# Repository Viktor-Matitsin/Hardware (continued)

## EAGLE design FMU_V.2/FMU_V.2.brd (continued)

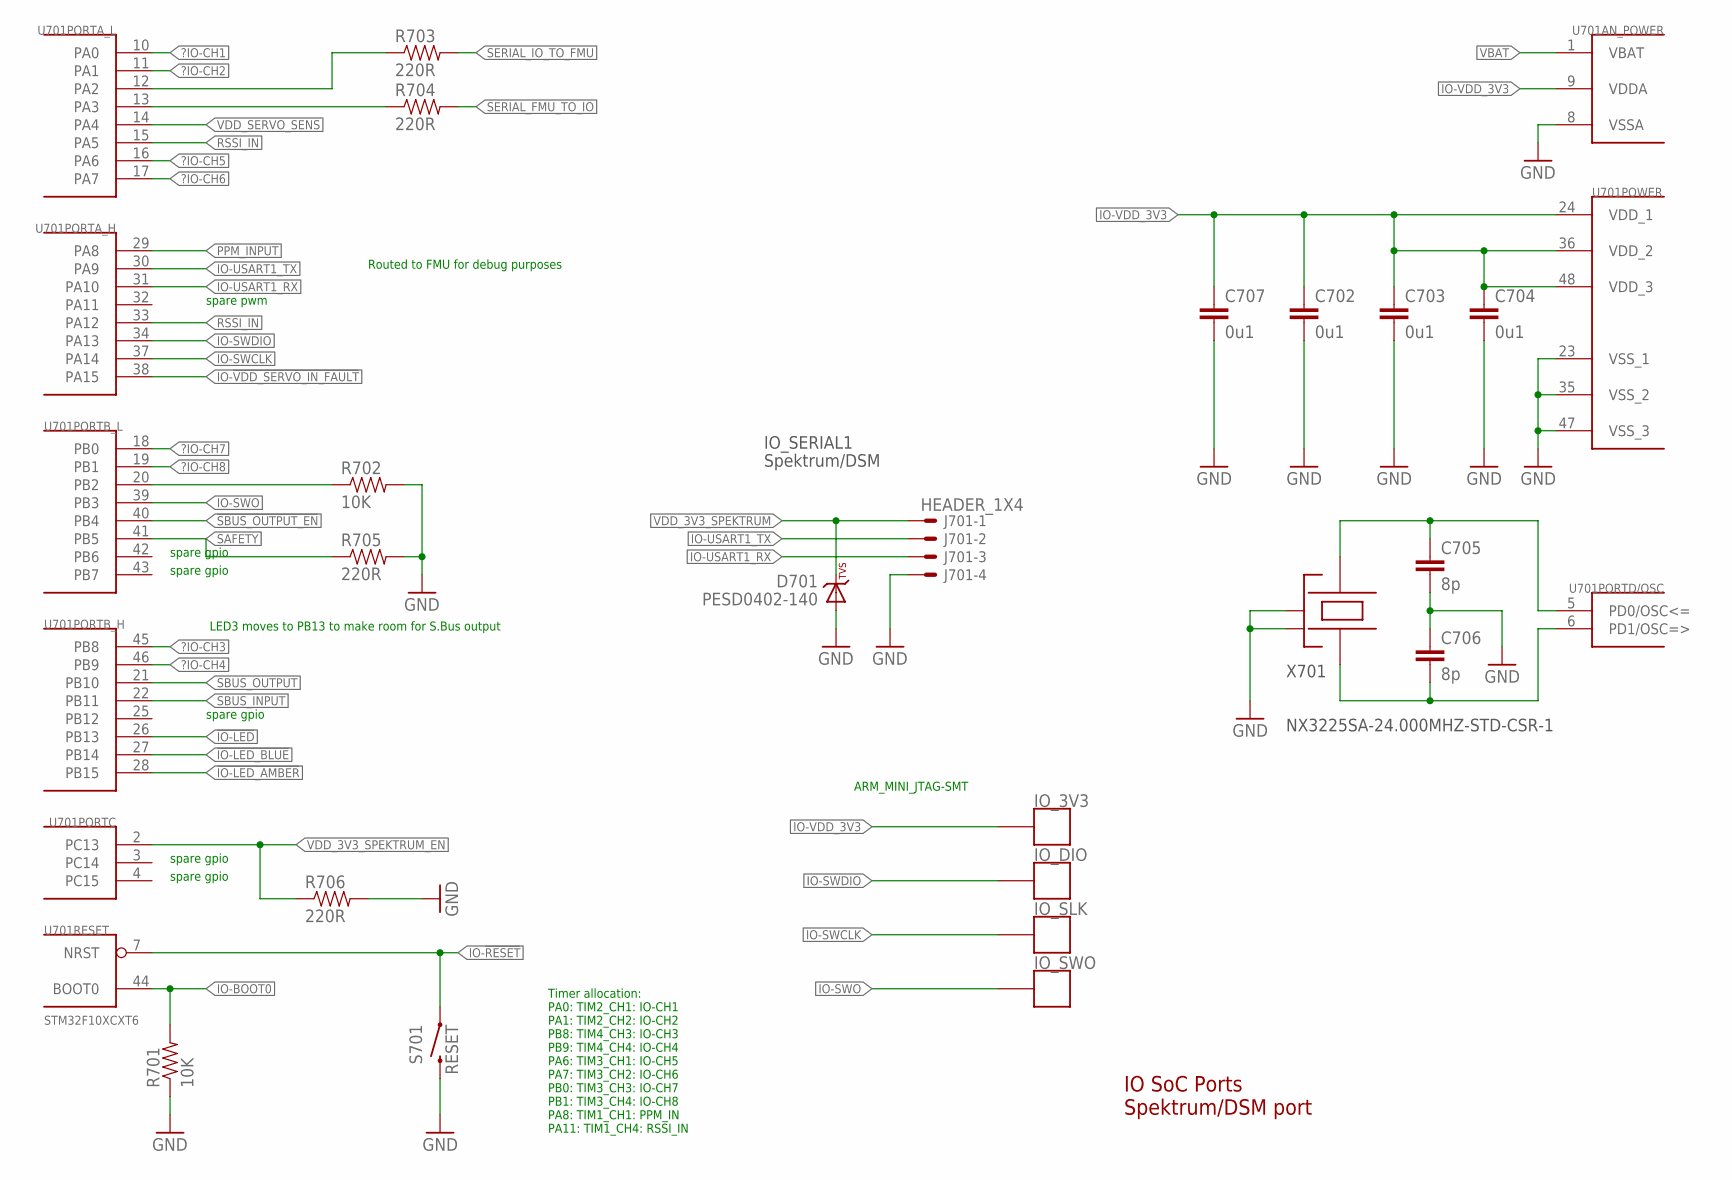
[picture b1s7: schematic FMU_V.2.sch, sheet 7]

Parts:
C702, C703, C704, C707: 0u1; 0603-CAP
C705, C706: 8p; 0603-CAP
D701: PESD0402-140; 0402-TVS; PARTNO PESD0402-140
IO_3V3: PAD.04; PAD.04X.04
IO_DIO: PAD.04; PAD.04X.04
IO_SLK: PAD.04; PAD.04X.04
IO_SWO: PAD.04; PAD.04X.04
J701: HEADER_1X4; HEADER_2.54MM-1X04
R701, R702: 10K; 0603-RES
R703, R704, R705, R706: 220R; 0603-RES
S701: RESET; EVQP7J01K; PARTNO EVQ-P7J01P
U701: STM32F10XCXT6; TQFP48; PARTNO STM32F100C8T6B
X701: NX3225SA-24.000MHZ-STD-CSR-1; OSCILLATOR-3.2X2.5; PARTNO NX3225SA-24.000000MHZ

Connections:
!IO-LED: U701.26 (PB13)
!IO-LED_AMBER: U701.28 (PB15); also elsewhere on the board
!IO-LED_BLUE: U701.27 (PB14); also elsewhere on the board
!SBUS_OUTPUT_EN: U701.40 (PB4)
?IO-CH1: U701.10 (PA0)
?IO-CH2: U701.11 (PA1)
?IO-CH3: U701.45 (PB8)
?IO-CH4: U701.46 (PB9)
?IO-CH5: U701.16 (PA6)
?IO-CH6: U701.17 (PA7)
?IO-CH7: U701.18 (PB0)
?IO-CH8: U701.19 (PB1)
GND: C702.P$2 (2), C703.P$2 (2), C704.P$2 (2), C705.P$2 (2), C706.P$1 (1), C707.P$2 (2), D701.A, J701.4, R701.1, R702.2, R705.2, R706.2, S701.B3 (2), U701.8 (VSSA), U701.23 (VSS_1), U701.35 (VSS_2), U701.47 (VSS_3), X701.2 (NC_2), X701.4 (NC_4); also elsewhere on the board
IO-!RESET: S701.A1 (1), U701.7 (NRST)
IO-!VDD_SERVO_IN_FAULT: U701.38 (PA15)
IO-BOOT0: R701.2, U701.44 (BOOT0); also elsewhere on the board
IO-BOOT1: R702.1, U701.20 (PB2)
IO-SWCLK: IO_SLK.P$1, U701.37 (PA14)
IO-SWDIO: IO_DIO.P$1, U701.34 (PA13)
IO-SWO: IO_SWO.P$1, U701.39 (PB3)
IO-USART1_RX: J701.3, U701.31 (PA10)
IO-USART1_TX: J701.2, U701.30 (PA9); also elsewhere on the board
IO-VDD_3V3: C702.P$1 (1), C703.P$1 (1), C704.P$1 (1), C707.P$1 (1), IO_3V3.P$1, U701.9 (VDDA), U701.24 (VDD_1), U701.36 (VDD_2), U701.48 (VDD_3); also elsewhere on the board
unnamed: R704.1, U701.13 (PA3)
unnamed: R703.1, U701.12 (PA2)
unnamed: C706.P$2 (2), U701.6 (PD1/OSC=>), X701.1
unnamed: C705.P$1 (1), U701.5 (PD0/OSC<=), X701.3
PPM_INPUT: U701.29 (PA8)
RSSI_IN: U701.15 (PA5), U701.33 (PA12)
SAFETY: R705.1, U701.41 (PB5)
SBUS_INPUT: U701.22 (PB11)
SBUS_OUTPUT: U701.21 (PB10)
SERIAL_FMU_TO_IO: R704.2; also elsewhere on the board
SERIAL_IO_TO_FMU: R703.2; also elsewhere on the board
VBAT: U701.1 (VBAT); also elsewhere on the board
VDD_3V3_SPEKTRUM: D701.C, J701.1; also elsewhere on the board
VDD_3V3_SPEKTRUM_EN: R706.1, U701.2 (PC13)
VDD_SERVO_SENS: U701.14 (PA4); also elsewhere on the board

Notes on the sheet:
IO SoC Ports Spektrum/DSM port
LED3 moves to PB13 to make room for S.Bus output
Routed to FMU for debug purposes
IO_SERIAL1
Spektrum/DSM
Timer allocation: PA0: TIM2_CH1: IO-CH1 PA1: TIM2_CH2: IO-CH2 PB8: TIM4_CH3: IO-CH3 PB9: TIM4_CH4: IO-CH4 PA6: TIM3_CH1: IO-CH5 PA7: TIM3_CH2: IO-CH6 PB0: TIM3_CH3: IO-CH7 PB1: TIM3_CH4: IO-CH8 PA8: TIM1_CH1: PPM_IN PA11: TIM1_CH4: RSSI_IN
spare pwm
spare gpio
ARM_MINI_JTAG-SMT

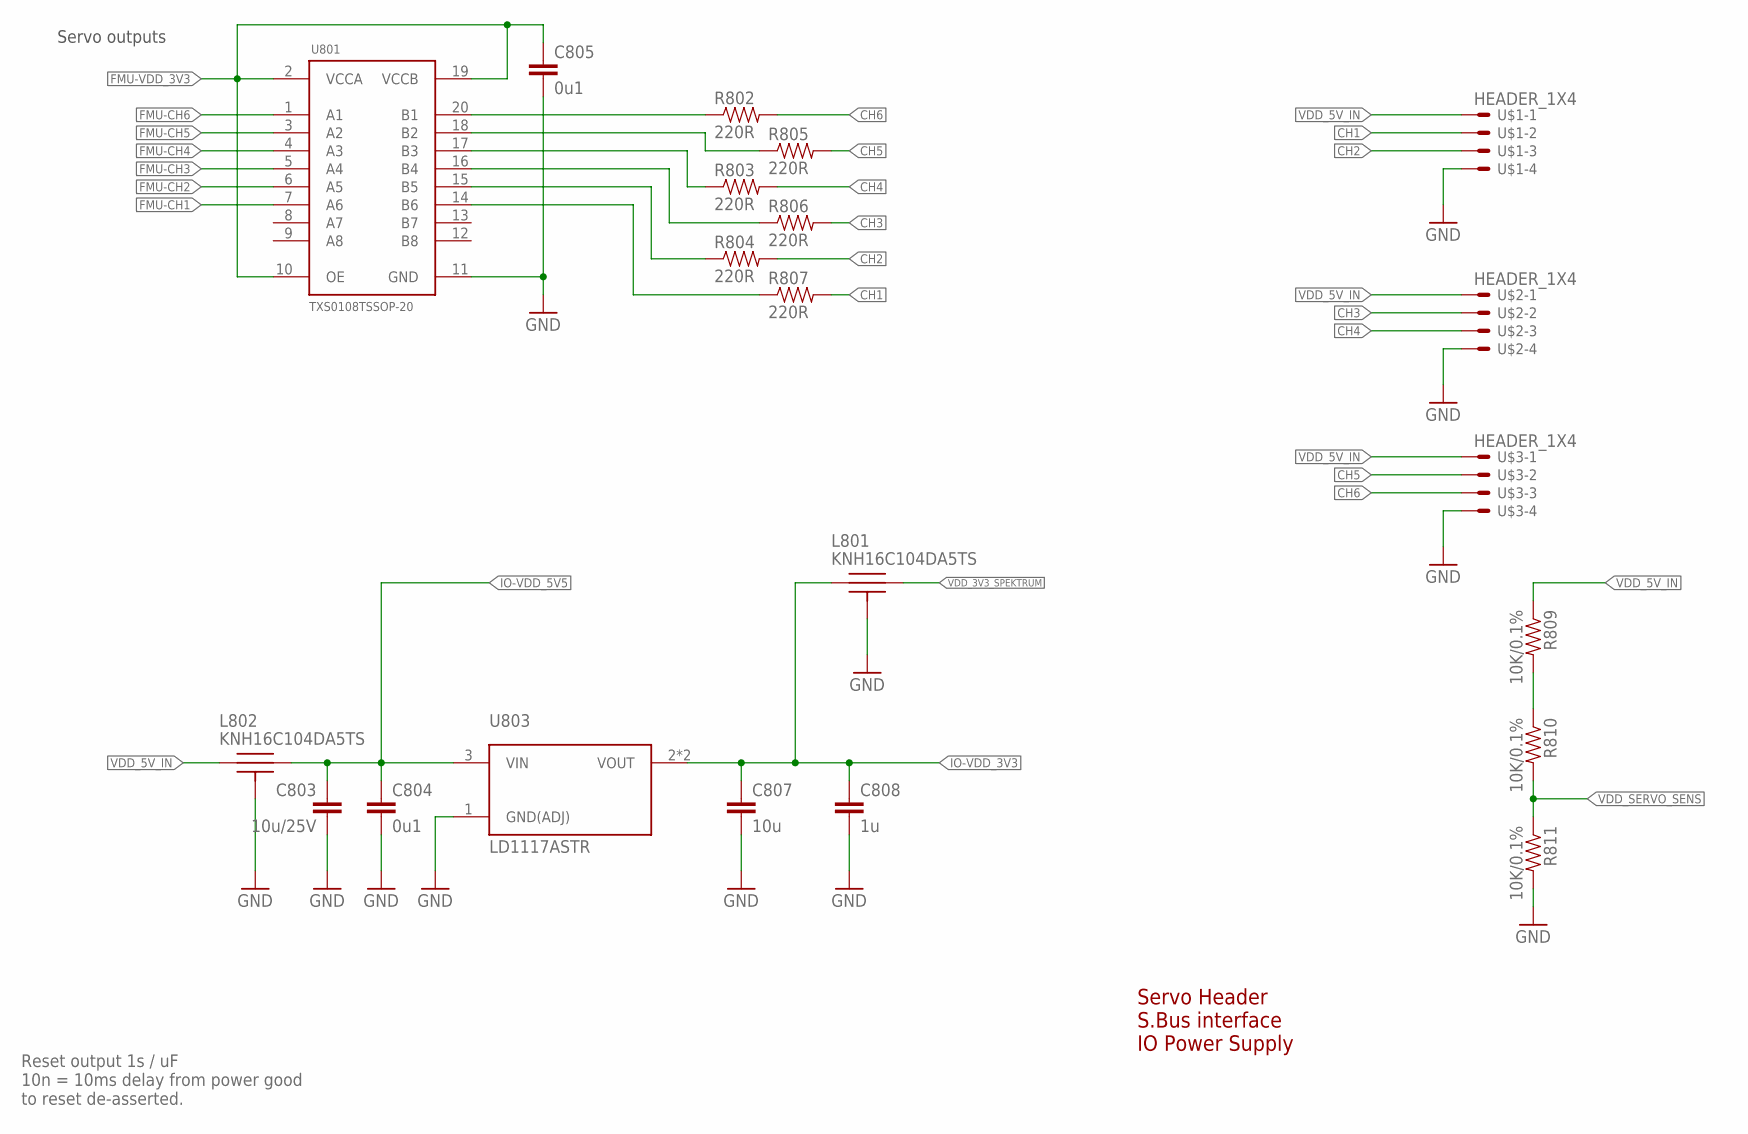
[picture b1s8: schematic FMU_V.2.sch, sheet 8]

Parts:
C803: 10u/25V; 0805-CAP
C804, C805: 0u1; 0603-CAP
C807: 10u; 0603-CAP
C808: 1u; 0603-CAP
L801, L802: KNH16C104DA5TS; KYOCERA-KNH16-DA
R802, R803, R804, R805, R806, R807: 220R; 0603-RES
R809, R810, R811: 10K/0.1%; 0603-RES
U801: TXS0108TSSOP-20; R-PDSO-G20
U803: LD1117ASTR; SOT-223
U$1, U$2, U$3: HEADER_1X4; HEADER_2.54MM-1X04

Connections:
CH1: R807.2, U$1.2
CH2: R804.2, U$1.3
CH3: R806.2, U$2.2
CH4: R803.2, U$2.3
CH5: R805.2, U$3.2
CH6: R802.2, U$3.3
FMU-CH1: U801.7 (A6); also elsewhere on the board
FMU-CH2: U801.6 (A5); also elsewhere on the board
FMU-CH3: U801.5 (A4); also elsewhere on the board
FMU-CH4: U801.4 (A3); also elsewhere on the board
FMU-CH5: U801.3 (A2); also elsewhere on the board
FMU-CH6: U801.1 (A1); also elsewhere on the board
FMU-VDD_3V3: C805.P$1 (1), U801.2 (VCCA), U801.10 (OE), U801.19 (VCCB); also elsewhere on the board
GND: C803.P$2 (2), C804.P$2 (2), C805.P$2 (2), C807.P$2 (2), C808.P$2 (2), L801.P$3, L801.P$4, L801.P$5, L802.P$3, L802.P$4, L802.P$5, R811.2, U801.11 (GND), U803.1 (GND(ADJ)), U$1.4, U$2.4, U$3.4; also elsewhere on the board
IO-VDD_3V3: C807.P$1 (1), C808.P$1 (1), L801.P$1, U803.2 (VOUT), U803.4 (VOUT); also elsewhere on the board
IO-VDD_5V5: C803.P$1 (1), C804.P$1 (1), L802.P$2, U803.3 (VIN); also elsewhere on the board
unnamed: R809.2, R810.1
unnamed: R802.1, U801.20 (B1)
unnamed: R805.1, U801.18 (B2)
unnamed: R803.1, U801.17 (B3)
unnamed: R806.1, U801.16 (B4)
unnamed: R804.1, U801.15 (B5)
unnamed: R807.1, U801.14 (B6)
VDD_3V3_SPEKTRUM: L801.P$2; also elsewhere on the board
VDD_5V_IN: L802.P$1, R809.1, U$1.1, U$2.1, U$3.1; also elsewhere on the board
VDD_SERVO_SENS: R810.2, R811.1; also elsewhere on the board

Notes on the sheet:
Servo Header S.Bus interface IO Power Supply
Servo outputs
Reset output 1s / uF 10n = 10ms delay from power good to reset de-asserted.

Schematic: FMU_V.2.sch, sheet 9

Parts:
C333, C334: 0u1; 0805-CAP
C901, C902, C903, C904, C905, C906, C907, C908: 22u; 1812-CAP
C909*, C910*, C921*, C922*: CAP0805; 0805-CAP
C911, C912, C923, C924: 330p; 0805-CAP
C913, C914, C918, C920: 0u01; 0805-CAP
C915, C916: 0u47/16V; 0805-CAP
C917, C919: 0u022; 0805-CAP
C925, C926, C927, C929, C930, C931: 100u; 1206-CAP
C928, C932: 33u; 1206-CAP
D901, D902, D903, D904: 6CWQ10FN-M3; DPAK
D909: 30BQ100; SMA-DIODE
J901, J902: HEADER_1X4; HEADER_2.54MM-1X04
L901, L902: DR120-330/33uH; SLF10145
L903, L904: KNH16C104DA5TS; KYOCERA-KNH16-DA; PARTNO KNH16C104DA5TS
LED6: ARG1608GKC/T; 0603-LED
R901, R902: 1M; 0603-RES
R903, R904: 22K/1%; 0603-RES
R905*, R906*, R907*, R908*: RESISTOR0805; 0805
R910, R911: 21K; 0805
R912, R913: 49K9; 0805
R914, R915: 1K65; 0805
R916, R917: 10R; R2512
R918, R919: 5K11; 0805
R921: 330R; 0603-RES
SYNC, SYNC1: PAD.03; PAD.03X.03
U901, U902: LM5005; TSSOP20
U$4: HEADER_1X4; HEADER_2.54MM-1X04

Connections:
BATT_CURRENT_SENS: R903.2; also elsewhere on the board
BATT_VOLTAGE_SENS: R904.2; also elsewhere on the board
CURRENT: L903.P$1, R902.2, U$4.2
GND: C333.P$2 (2), C334.P$2 (2), C901.2, C902.2, C903.2, C904.2, C905.2, C906.2, C907.2, C908.2, C909*.P$2 (2), C910*.P$2 (2), C911.P$2 (2), C912.P$2 (2), C913.P$2 (2), C914.P$2 (2), C915.P$2 (2), C916.P$2 (2), C925.P$2 (2), C926.P$2 (2), C927.P$2 (2), C928.P$2 (2), C929.P$2 (2), C930.P$2 (2), C931.P$2 (2), C932.P$2 (2), J901.3, J901.4, J902.3, J902.4, L903.P$3, L903.P$4, L903.P$5, L904.P$3, L904.P$4, L904.P$5, R901.1, R902.1, R906*.1, R908*.1, R910.1, R911.1, R914.1, R915.1, R916.2, R917.2, R921.1, U901.10 (AGND), U901.13 (PGND1), U901.14 (PGND), U902.10 (AGND), U902.13 (PGND1), U902.14 (PGND), U$4.4; also elsewhere on the board
unnamed: C918.P$1 (1), R912.1
unnamed: LED6.C, R921.2
unnamed: C920.P$1 (1), R913.1
unnamed: C911.P$1 (1), U901.9 (RAMP)
unnamed: D903.1 (A1), D903.3 (A2), U901.15 (IS), U901.16 (IS1)
unnamed: SYNC.P$1, U901.5 (SYNC)
unnamed: C909*.P$1 (1), R905*.1, R906*.2, U901.2 (SD)
unnamed: C913.P$1 (1), U901.11 (SS)
unnamed: D901.1 (A1), D901.3 (A2), J901.1, J901.2
unnamed: C901.1, C902.1, C903.1, C904.1, D901.4 (C), R905*.2, U901.3 (VIN), U901.4 (VIN1)
unnamed: C334.P$1 (1), C929.P$1 (1), C930.P$1 (1), C931.P$1 (1), C932.P$1 (1), D909.A, L902.P$2 (2), LED6.A, R919.2, U902.12 (OUT)
unnamed: C917.P$2 (2), C923.P$1 (1), D903.4 (C), L901.P$1 (1), U901.17 (SW), U901.18 (SW1), U901.19 (PRE)
unnamed: C915.P$1 (1), U901.1 (VCC)
unnamed: L904.P$2, R904.1
unnamed: L903.P$2, R903.1
unnamed: C905.1, C906.1, C907.1, C908.1, D902.4 (C), R907*.2, U902.3 (VIN), U902.4 (VIN1)
unnamed: R910.2, U901.8 (RT)
unnamed: C917.P$1 (1), U901.20 (BST)
unnamed: C923.P$2 (2), R916.1
unnamed: C916.P$1 (1), U902.1 (VCC)
unnamed: C921*.P$1 (1), R912.2, R914.2, R918.1, U901.7 (FB)
unnamed: C918.P$2 (2), C921*.P$2 (2), U901.6 (COMP)
unnamed: R911.2, U902.8 (RT)
unnamed: C914.P$1 (1), U902.11 (SS)
unnamed: C912.P$1 (1), U902.9 (RAMP)
unnamed: SYNC1.P$1, U902.5 (SYNC)
unnamed: C910*.P$1 (1), R907*.1, R908*.2, U902.2 (SD)
unnamed: D902.1 (A1), D902.3 (A2), J902.1, J902.2
unnamed: D904.1 (A1), D904.3 (A2), U902.15 (IS), U902.16 (IS1)
unnamed: C919.P$2 (2), C924.P$1 (1), D904.4 (C), L902.P$1 (1), U902.17 (SW), U902.18 (SW1), U902.19 (PRE)
unnamed: C919.P$1 (1), U902.20 (BST)
unnamed: C924.P$2 (2), R917.1
unnamed: C922*.P$1 (1), R913.2, R915.2, R919.1, U902.7 (FB)
unnamed: C920.P$2 (2), C922*.P$2 (2), U902.6 (COMP)
VDD_5V_IN: C333.P$1 (1), C925.P$1 (1), C926.P$1 (1), C927.P$1 (1), C928.P$1 (1), D909.C, L901.P$2 (2), R918.2, U901.12 (OUT); also elsewhere on the board
VOLTAGE: L904.P$1, R901.2, U$4.3

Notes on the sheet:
Power source selector
1V_+51V
2V_+51V

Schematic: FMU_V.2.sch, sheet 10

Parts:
DM: PAD.04; PAD.04X.04; PARTNO *
DP: OTG_FS_DP; PAD.04X.04; PARTNO *
F-BOOT: PAD.04; PAD.04X.04; PARTNO *
GND: PAD.04; PAD.04X.04; PARTNO *
IO-BOOT0: PAD.04; PAD.04X.04; PARTNO *
JP3, JP4: FIDUCIAL1.5X3; FIDUCIAL-1.5X3
M3_MOUNT1, M3_MOUNT2, M3_MOUNT3, M3_MOUNT4: MOUNT-HOLE3.1MM; MOUNT-HOLE3.1; PARTNO *
VDDA_3V3: PAD.04; PAD.04X.04; PARTNO *
VDD_5V_IN: PAD.04; PAD.04X.04; PARTNO *

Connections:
FMU-BOOT0: F-BOOT.P$1; also elsewhere on the board
GND: GND.P$1; also elsewhere on the board
IO-BOOT0: IO-BOOT0.P$1; also elsewhere on the board
OTG_FS_DM: DM.P$1; also elsewhere on the board
OTG_FS_DP: DP.P$1; also elsewhere on the board
VDD_3V3_SENSORS: VDDA_3V3.P$1; also elsewhere on the board
VDD_5V_IN: VDD_5V_IN.P$1; also elsewhere on the board

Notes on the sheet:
Production Testing Pads
Test and Fiducials
Fiducials for machine vision alignment.
POWER
STATUS AND ANALOG

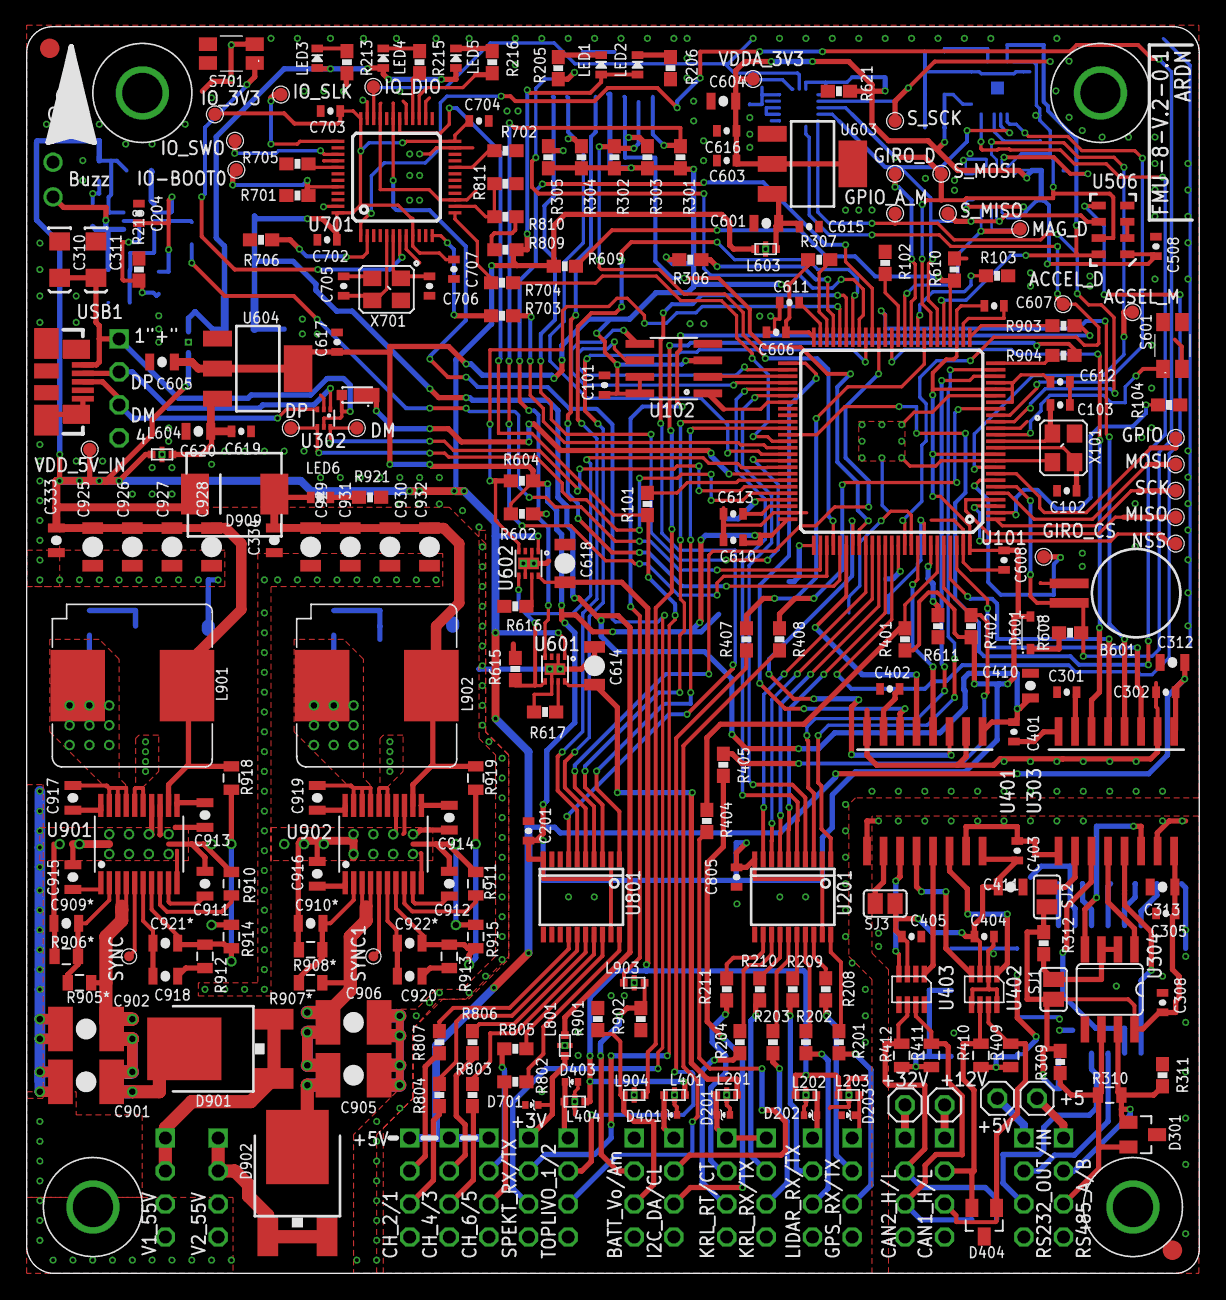
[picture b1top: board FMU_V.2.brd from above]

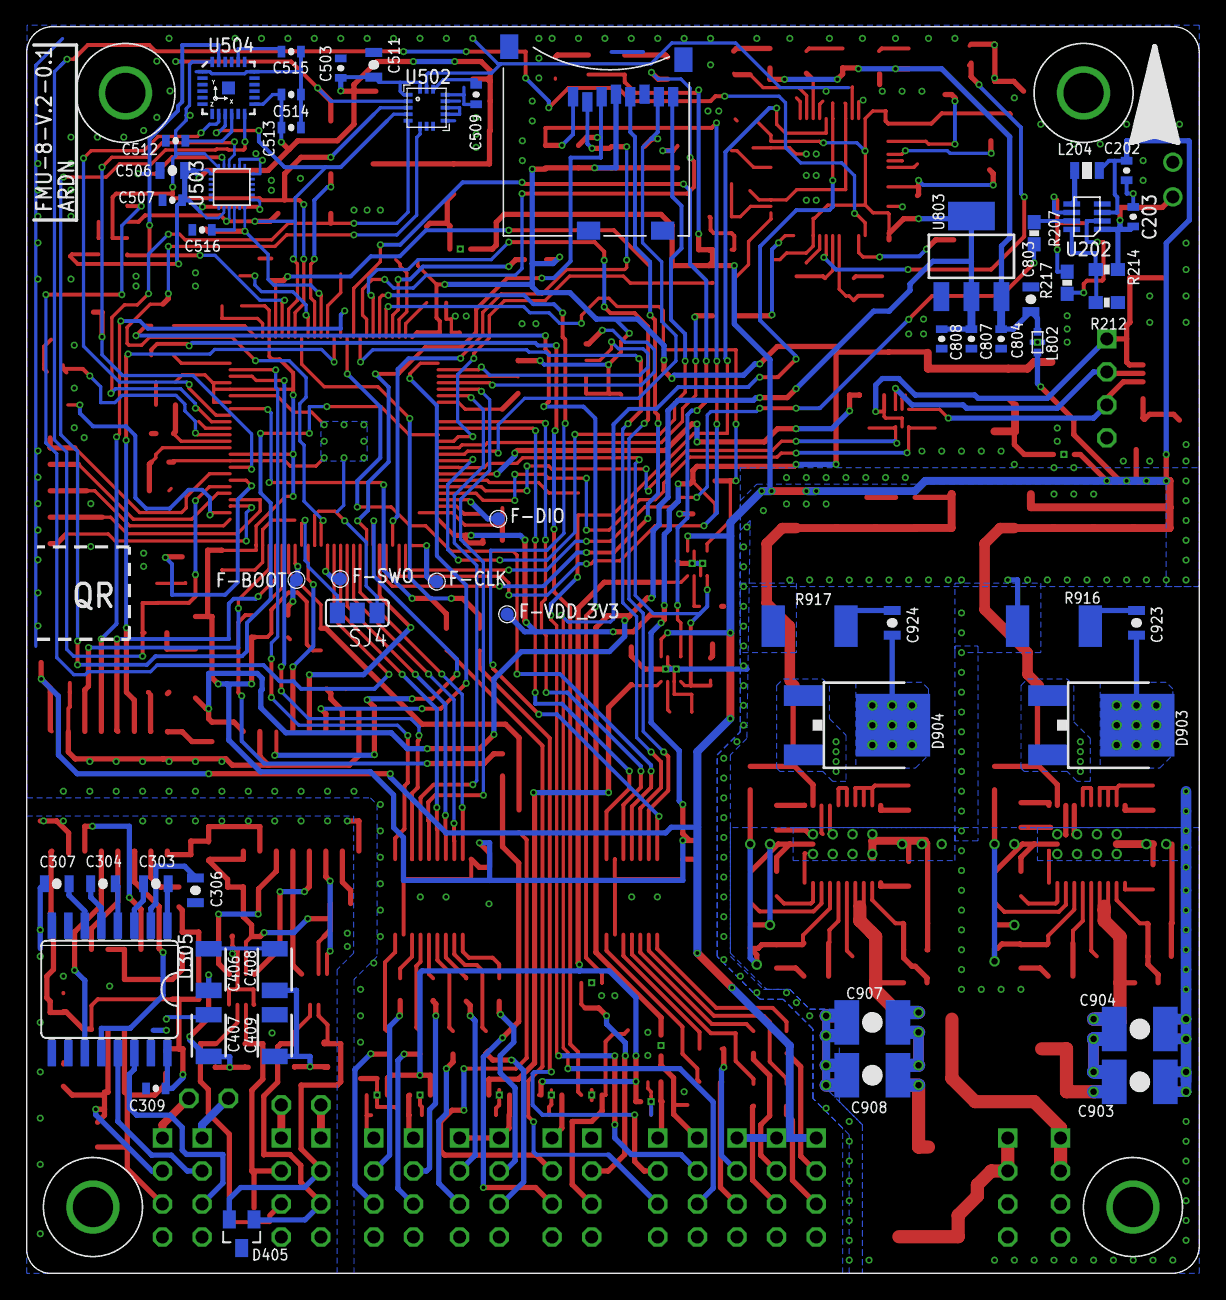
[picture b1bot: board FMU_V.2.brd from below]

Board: 2 copper layers, 90.2 x 95.9 mm, 322 parts (56 on the bottom side), 244 nets.

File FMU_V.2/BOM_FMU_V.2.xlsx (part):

Oty | Value | Device | Package | Parts | Description | LINK
1 | 0u01 | CAP0603 | 0603-CAP | C515 | Capacitor | https://www.digikey.com/product-detail/en/kemet/C0603C103K3R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
4 | 0u01 | CAP0805 | 0805-CAP | C913, C914, C918, C920 | Capacitor | https://www.digikey.com/product-detail/en/kemet/C0805C103K3R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
2 | 0u022 | CAP0805 | 0805-CAP | C917, C919 | Capacitor | https://www.digikey.com/product-detail/en/kemet/C0805C223K3R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
32 | 0u1 | CAP0603 | 0603-CAP | C101, C201, C301, C302, C305, C308, C309, C401, C402, C403, C404, C405, C503, C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 | Capacitor | https://www.digikey.com/product-detail/en/kemet/C0603C104K3R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
2 | 0u1 | CAP0805 | 0805-CAP | C333, C334 | Capacitor | https://www.digikey.com/product-detail/en/tdk-corporation/C2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
4 | 0u33 | CAP1210 | 1210-CAP | C406, C407, C408, C409 | Capacitor | https://www.digikey.com/product-detail/en/kemet/C1210C334K1R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
2 | 0u47 | CAP0603 | 0603-CAP | C204, C509 | Capacitor | https://www.digikey.com/product-detail/en/kemet/C0603C474K3R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
2 | 0u47 | CAP0805 | 0805-CAP | C915, C915 | Capacitor | https://www.digikey.com/product-detail/en/kemet/C0805C474K5R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
8 | 100u | CAP1206 | 1206-CAP | C925, C926, C927, C929, C930, C931, C614, C618 | Capacitor | https://www.digikey.com/product-detail/en/taiyo-yuden/EMK325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
2 | 100u | CAP_POL1206 | EIA3216 | C310, C311 | Capacitor | https://www.digikey.com/product-detail/en/avx-corporation/TL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
1 | 10u | CAP0603 | 0603-CAP | C807 | Capacitor | https://www.digikey.com/product-detail/en/kemet/C0603C106M9P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
7 | 10u/25V | CAP0805 | 0805-CAP | C312, C410, C506, C511, C803, C601, C620 | Capacitor | https://www.digikey.com/product-detail/en/kemet/C0805C106K3P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
3 | 1u | CAP0603 | 0603-CAP | C202, C808, C603 | Capacitor | https://www.digikey.com/product-detail/en/kemet/C0603C105K3R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
4 | 1u | CAP0805 | 0805-CAP | C303, C304, C306, C307 | Capacitor | https://www.digikey.com/product-detail/en/kemet/C0805C105K3R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
4 | 22u/25V | CAP0805 | 0805-CAP | C313, C411, C604, C605 | Capacitor | https://www.digikey.com/product-detail/en/murata-electronics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
4 | 2u2 | CAP0603 | 0603-CAP | C512, C513, C611, C613 | Capacitor | https://www.digikey.com/product-detail/en/kemet/C0603C225K4P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
4 | 330p | CAP0805 | 0805-CAP | C911, C912, C923, C924 | Capacitor | https://www.digikey.com/product-detail/en/kemet/C0805C331K1R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
2 | 33u | CAP1206 | 1206 | C928, C932 | Capacitor | https://www.digikey.com/product-detail/en/kemet/C1206C476M8P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
8 | 22u | CAP1812 | 1812-CAP | C901, C902,C903, C904, C905, C906, C907, C908 | Capacitor | https://www.digikey.com/product-detail/en/tdk-corporation/CK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
1 | 5n6 | CAP0603 | 0603-CAP | C203 | Capacitor | https://www.digikey.com/product-detail/en/kemet/C0603C562K5R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
4 | 8p | CAP0603 | 0603-CAP | C102, C103, C705, C706 | Capacitor | https://www.digikey.com/product-detail/en/kemet/CBR06C809BAG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
6 | 100K | RESISTOR0603-RES | 0603-RES | R214, R301, R302, R303, R304, R305 | Resistor | https://www.digikey.com/product-detail/en/vishay-dale/CRCW06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
8 | 10K | RESISTOR0603-RES | 0603-RES | R102, R103, R212, R611, R615, R701, R702, R706 | Resistor | https://www.digikey.com/product-detail/en/vishay-dale/CRCW06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
7 | 10K/0,1% | RESISTOR0603-RES | 0603-RES | R407, R408, R609, R610, R809, R810, R811 | Resistor | https://www.digikey.com/product-detail/en/vishay-dale/TNPW06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
2 | 10R | RESISTOR2512-RES | 2512-RES | R916, R917 | Resistor | https://www.digikey.com/product-detail/en/vishay-dale/CRCW25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
10 | 120R | RESISTOR0603-RES | 0603-RES | R201, R202, R203, R204, R208, R209, R210, R211, R404, R405 | Resistor | https://www.digikey.com/product-detail/en/vishay-dale/CRCW06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
1 | 120R | RESISTOR0805-RES | 0805-RES | R310 | Resistor | https://www.digikey.com/product-detail/en/vishay-dale/CRCW08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
2 | 16K5 | RESISTOR0603-RES | 0603-RES | R218, R617 | Resistor | https://www.digikey.com/product-detail/en/vishay-dale/CRCW06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
1 | 1K | RESISTOR0603-RES | 0603-RES | R608 | Resistor | https://www.digikey.com/product-detail/en/vishay-dale/CRCW06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
3 | 1K2 | RESISTOR0603-RES | 0603-RES | R309, R311, R312 | Resistor | https://www.digikey.com/product-detail/en/vishay-dale/CRCW06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
4 | 1K5 | RESISTOR0603-RES | 0603-RES | R401, R402, R306, R307 | Resistor | https://www.digikey.com/product-detail/en/vishay-dale/CRCW06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
2 | 1K65 | RESISTOR0805-RES | 0805-RES | R914, R915 | Resistor | https://www.digikey.com/product-detail/en/vishay-dale/CRCW08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
5 | 1M | RESISTOR0603-RES | 0603-RES | R104, R602, R604, R901, R902 | Resistor | https://www.digikey.com/product-detail/en/vishay-dale/RCS060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
2 | 21K | RESISTOR0805-RES | 0805-RES | R910, R911 | Resistor | https://www.digikey.com/product-detail/en/yageo/RC0603FR-072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
10 | 220R | RESISTOR0603-RES | 0603-RES | R621, R703, R704, R705, R802, R803, R804, R805, R806, R807 | Resistor | https://www.digikey.com/product-detail/en/vishay-dale/CRCW06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
2 | 22K/1% | RESISTOR0603-RES | 0603-RES | R903, R904 | Resistor | https://www.digikey.com/product-detail/en/vishay-dale/CRCW06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
2 | 22K | RESISTOR0603-RES | 0603-RES | R903, R904 | Resistor | https://www.digikey.com/product-detail/en/yageo/RC0603JR-072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
1 | 25K5 | RESISTOR0603-RES | 0603-RES | R616 | Resistor | https://www.digikey.com/product-detail/en/vishay-dale/CRCW06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
4 | 330R | RESISTOR0603-RES | 0603-RES | R206, R213, R216, R921 | Resistor | https://www.digikey.com/product-detail/en/vishay-dale/CRCW06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
1 | 453K | RESISTOR0603-RES | 0603-RES | R217 | Resistor | https://www.digikey.com/product-detail/en/vishay-dale/CRCW06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
1 | 470R | RESISTOR0603-RES | 0603-RES | R101 | Resistor | https://www.digikey.com/product-detail/en/vishay-dale/CRCW06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
2 | 49K9 | RESISTOR0805-RES | 0805-RES | R912, R913 | Resistor | https://www.digikey.com/product-detail/en/vishay-dale/CRCW08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
2 | 510R | RESISTOR0603-RES | 0603-RES | R205, R215 | Resistor | https://www.digikey.com/product-detail/en/vishay-dale/CRCW06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
2 | 5K11 | RESISTOR0805-RES | 0805-RES | R918, R919 | Resistor | https://www.digikey.com/product-detail/en/vishay-dale/CRCW08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
4 | 60R | RESISTOR0805-RES | 0805-RES | R409, R410, R411, R412 | Resistor | https://www.digikey.com/product-detail/en/vishay-dale/CRCW08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
1 | 9K09 | RESISTOR0603-RES | 0603-RES | R207 | Resistor | https://www.digikey.com/product-detail/en/vishay-dale/TNPW06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
1 | 2908-05WB-MG | MICROSDSDI | MICROSD | U301 | CONN MICRO SD CARD PUSH-PUSH R/A | https://www.digikey.com/product-detail/en/3m/2908-05WB-MG/3M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
2 | ADUM5402CRWZ-RL | ADUM1301 | SO-16W | U303, U401 | DGTL ISO 2.5KV GEN PURP 16SOIC | https://www.digikey.com/product-detail/en/analog-devices-inc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
2 | BQ24315DSGR | BQ24315 | QFN8-DSG | U601, U602 | IC LI+ CHARGER FRONT END 8-SON | https://www.digikey.com/product-detail/en/texas-instruments/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
1 | FM25V01A-G | FM25V01 | SO08 | U102 | IC FRAM 128KBIT 40MHZ 8SOIC | https://www.digikey.com/product-detail/en/cypress-semiconduc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
1 | ICM20608-G | ICM20608 | LGA-16-3PX5P | U502 | IMU ACCEL/GYRO I2C/SPI 16LGA | https://www.digikey.com/product-detail/en/tdk-invensense/ICM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
3 | LM1117IMPX-3.3/NOPB | LM1117 | TO-261-4 | U603, U604, U803 | IC REG LIN 3.3V 800MA SOT223-4 | https://www.digikey.com/product-detail/en/texas-instruments/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
2 | LM5005MHX/NOPB | LM5005 | TSSOP20 | U901, U902 | IC REG BUCK ADJ 2.5A 20TSSOP | https://www.digikey.com/product-detail/en/texas-instruments/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
1 | LT3469ETS8 | LT3469 | SOT23-8 | U202 | IC AMP DVR W/REG 1.3MHZ TSOT23-8 | https://www.digikey.com/product-detail/en/linear-technology/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
1 | MAX13487EESA+T | MAX13487 | SO08 | U304 | IC TXRX RS485/RS422 8-SOIC | https://www.digikey.com/product-detail/en/maxim-integrated/M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
1 | MAX232ECWE | MAX232E | SO16L | U305 | IC TXRX RS232 5V ESD-PROT 16SOIC | https://www.digikey.com/product-detail/en/maxim-integrated/M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
2 | MAX3051EKA+T | MAX3051 | SOT23-8 | U402, U403 | IC TXRX CAN 3.3V SOT23-8 | https://www.digikey.com/product-detail/en/maxim-integrated/M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
1 | MPU-6000 | MPU-6000 | QFN-24 (4x4x1 mm) | U504 | IMU ACCEL/GYRO I2C/SPI 24QFN | https://www.digikey.com/product-detail/en/tdk-invensense/MPU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
